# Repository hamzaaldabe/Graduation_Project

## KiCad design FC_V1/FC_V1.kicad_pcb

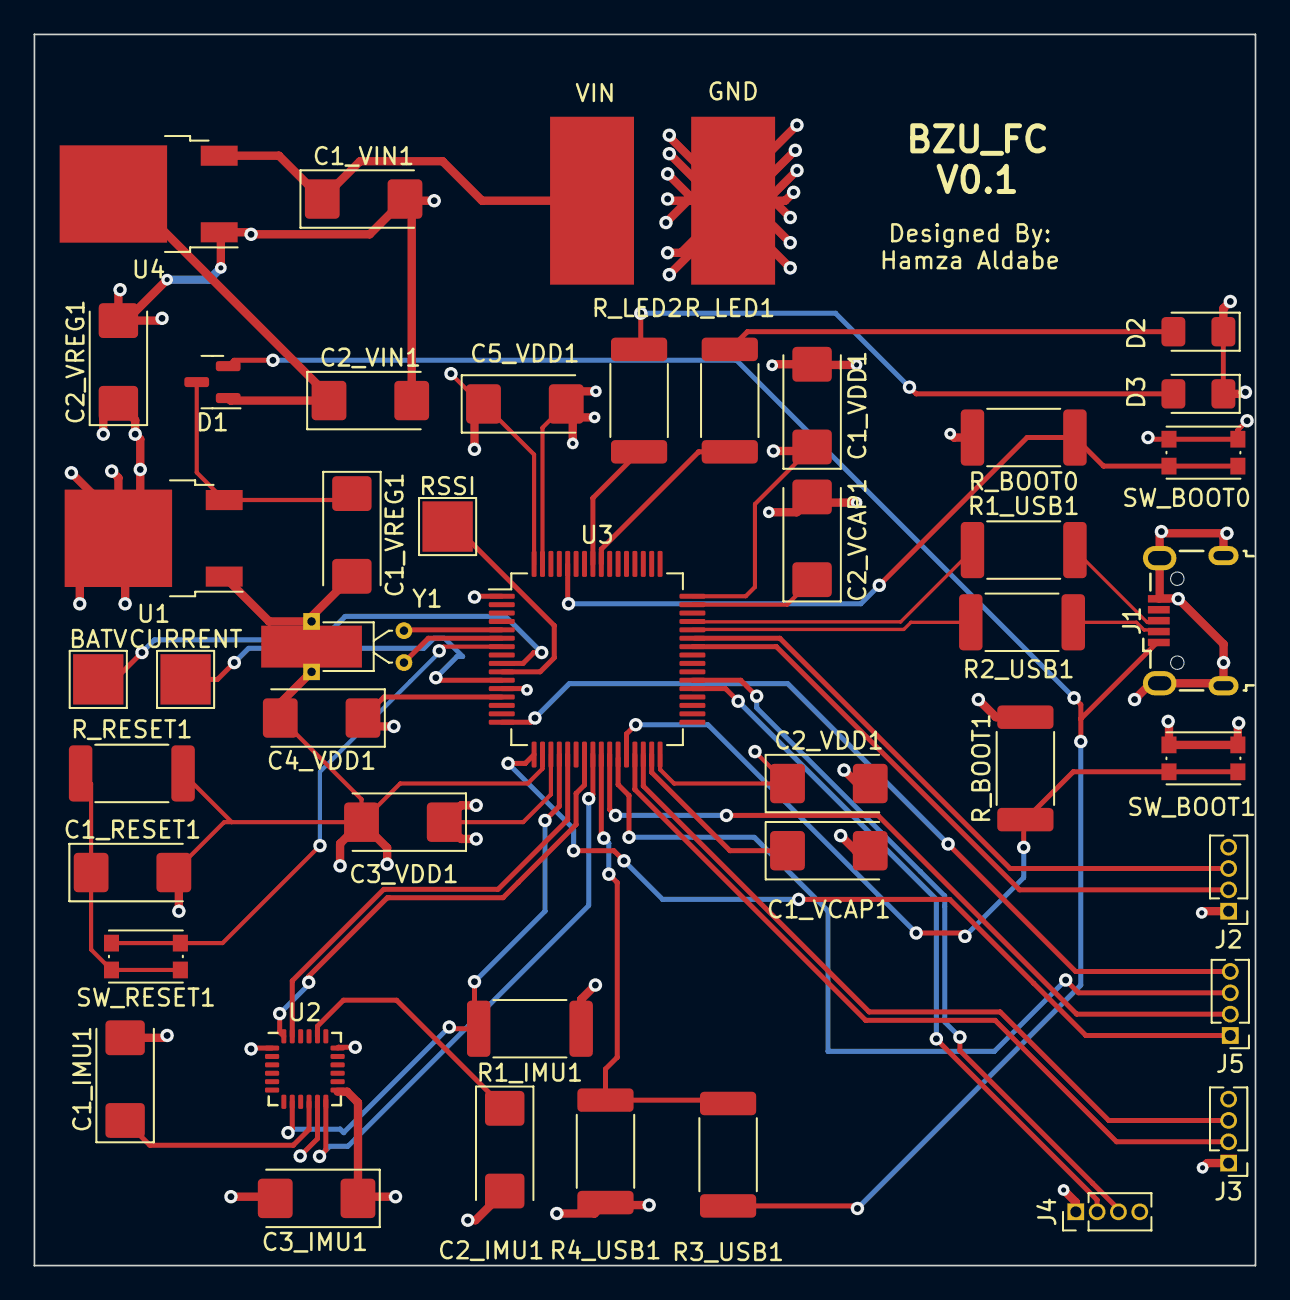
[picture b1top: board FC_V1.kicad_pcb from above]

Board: 4 copper layers, 72.7 x 73.3 mm, 46 parts (0 on the bottom side), 42 nets.

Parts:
BATV: TestPoint_Pad_3.0x3.0mm
C1_IMU1, C1_RESET1, C3_IMU1: 0.1uf; CP_EIA-6032-15_Kemet-U
C1_VCAP1, C1_VDD1, C2_VCAP1, C2_VDD1, C3_VDD1, C4_VDD1, C5_VDD1: 100nf; CP_EIA-6032-15_Kemet-U
C1_VIN1, C1_VREG1, C2_VIN1, C2_VREG1: 10uf; CP_EIA-6032-15_Kemet-U
C2_IMU1: 2.2uf; CP_EIA-6032-15_Kemet-U
CURRENT: TestPoint_Pad_3.0x3.0mm
D1: BAT54C; SOT-23
D2, D3: LED; LED_1206_3216Metric_Pad1.42x1.75mm_HandSolder
GND: SolderWirePad_1x01_SMD_5x10mm
J1: USB_B_Micro; USB_Micro-B_Wuerth_629105150521
J2, J3, J4, J5: Conn_01x04_Male; PinHeader_1x04_P1.27mm_Vertical
R1_IMU1, R3_USB1, R4_USB1: 10Kohm; R_2512_6332Metric_Pad1.40x3.35mm_HandSolder
R1_USB1, R2_USB1: 22ohm; R_2512_6332Metric_Pad1.40x3.35mm_HandSolder
RSSI: TestPoint_Pad_3.0x3.0mm
R_BOOT0, R_BOOT1: 10Kohm; R_2512_6332Metric_Pad1.40x3.35mm_HandSolder
R_LED1, R_LED2: 1Kohm; R_2512_6332Metric_Pad1.40x3.35mm_HandSolder
R_RESET1: 10Kohm; R_2512_6332Metric_Pad1.40x3.35mm_HandSolder
SW_BOOT0, SW_BOOT1: SW_Push; SW_Push_1P1T_NO_CK_KMR2
SW_RESET1: SW_Push; SW_Push_1P1T_NO_CK_KMR2
U1: NCP1117-3.3_TO252; TO-252-2
U2: MPU-6000; InvenSense_QFN-24_4x4mm_P0.5mm
U3: STM32F415RGTx; LQFP-64_10x10mm_P0.5mm
U4: NCP1117-5.0_TO252; TO-252-2
VIN: SolderWirePad_1x01_SMD_5x10mm
Y1: 8MHZ; Crystal_DS26_D2.0mm_L6.0mm_Horizontal_1EP_style2

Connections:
/5V_REG: C2_VIN1.1, D1.1, U4.2 (VO)
/5V_USB: D1.2, J1.1 (VBUS), R3_USB1.1
/BATV_PAD: BATV.1, U3.9 (PC1)
/BOOT0: R_BOOT0.1, SW_BOOT0.1, U3.60 (BOOT0)
/BOOT1: R_BOOT1.1, SW_BOOT1.1, U3.28 (PB2)
/CURRENT_PAD: CURRENT.1, U3.11 (PC3)
/D+: J1.3 (D+), R1_USB1.2
/D-: J1.2 (D-), R2_USB1.2
/IMU_CS: R1_IMU1.2, U2.8 (~CS), U3.20 (PA4)
/IMU_INT: U2.12 (INT), U3.24 (PC4)
/LED1: R_LED1.2, U3.56 (PB4)
/LED2: R_LED2.2, U3.57 (PB5)
/M1: J5.1, U3.17 (PA3)
/M2: J5.2, U3.26 (PB0)
/M3: J5.3, U3.27 (PB1)
/M4: J5.4, U3.16 (PA2)
/RESET: SW_RESET1.2, U3.7 (NRST)
/RSSI_PAD: RSSI.1, U3.10 (PC2)
/SCL_IMU: U2.23 (SCL/SCLK), U3.21 (PA5)
/SDA_IMU: U2.24 (SDA/MOSI), U3.23 (PA7)
/UART1_RX: J2.3, U3.43 (PA10)
/UART1_TX: J2.2, U3.42 (PA9)
/UART2_RX: J3.3, U3.30 (PB11)
/UART2_TX: J3.2, U3.29 (PB10)
/UART3_RX: J4.3, U3.38 (PC7)
/UART3_TX: J4.2, U3.37 (PC6)
/USBD+: R1_USB1.1, U3.45 (PA12)
/USBD-: R2_USB1.1, U3.44 (PA11)
/VDD: C1_VDD1.1, C2_VDD1.1, C2_VREG1.1, C3_IMU1.1, C3_VDD1.1, C4_VDD1.1, C5_VDD1.1, J2.1, J3.1, J4.1, R1_IMU1.1, SW_BOOT0.2, SW_BOOT1.2, U1.2 (VO), U2.13 (VDD), U3.1 (VBAT), U3.13 (VDDA), U3.19 (VDD), U3.32 (VDD), U3.48 (VDD), U3.64 (VDD)
/VIN: C1_VIN1.1, U4.3 (VI), VIN.2
GND: C1_IMU1.2, C1_RESET1.2, C1_VCAP1.2, C1_VDD1.2, C1_VIN1.2, C1_VREG1.2, C2_IMU1.2, C2_VCAP1.2, C2_VDD1.2, C2_VIN1.2, C2_VREG1.2, C3_IMU1.2, C3_VDD1.2, C4_VDD1.2, C5_VDD1.2, D2.1 (K), D3.1 (K), GND.1, J1.5 (GND), J1.6 (Shield), J2.4, J3.4, J4.4, R4_USB1.1, R_BOOT0.2, R_BOOT1.2, R_RESET1.2, U1.1 (GND), U2.1 (CLKIN), U2.11 (FSYNC), U2.18 (GND), U3.12 (VSSA), U3.18 (VSS), U3.63 (VSS), U4.1 (GND), Y1.3
unnamed: C1_IMU1.1, U2.10 (REGOUT)
unnamed: C1_RESET1.1, R_RESET1.1, SW_RESET1.1
unnamed: C1_VCAP1.1, U3.31 (VCAP_1)
unnamed: C1_VREG1.1, D1.3, U1.3 (VI)
unnamed: C2_IMU1.1, U2.20 (CPOUT)
unnamed: C2_VCAP1.1, U3.47 (VCAP_2)
unnamed: D2.2 (A), R_LED1.1
unnamed: D3.2 (A), R_LED2.1
unnamed: R3_USB1.2, R4_USB1.2, U3.25 (PC5)
unnamed: U3.5 (PH0), Y1.1
unnamed: U3.6 (PH1), Y1.2
